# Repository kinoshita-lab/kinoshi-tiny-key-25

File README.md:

# Kinoshi-Tiny Key 25
[日本語の説明はこちら](./README.ja.md)

----

## What is this?

- A small MIDI keyboard, 106 mm x 50 mm.
- Has USB MIDI (In/Out) and legacy MIDI (Out, 3.5 mm Type A).
- It has:
  - Octave switches +/-
  - Modulation switch
  - Pitch Bend switches
  - Sustain switch

- The source code and schematics are open. You can change them as you need.

## What's in the box
- DIN-TRS adapter cable (Type A)
- Rubber feet (use them if you need them)

## How to use
- Power it with a USB Type-C cable. Connect it to a mobile battery, a PC/Mac, etc.
- USB MIDI works with the standard OS driver. No extra driver is needed.

## Settings editor
- A web-browser-based editor lets you change the MIDI channels, velocity, button behavior and more.
- https://kinoshi-tiny-key-25.editor.kinoshita-lab.com/
- Requires firmware v1.1.0 or later.

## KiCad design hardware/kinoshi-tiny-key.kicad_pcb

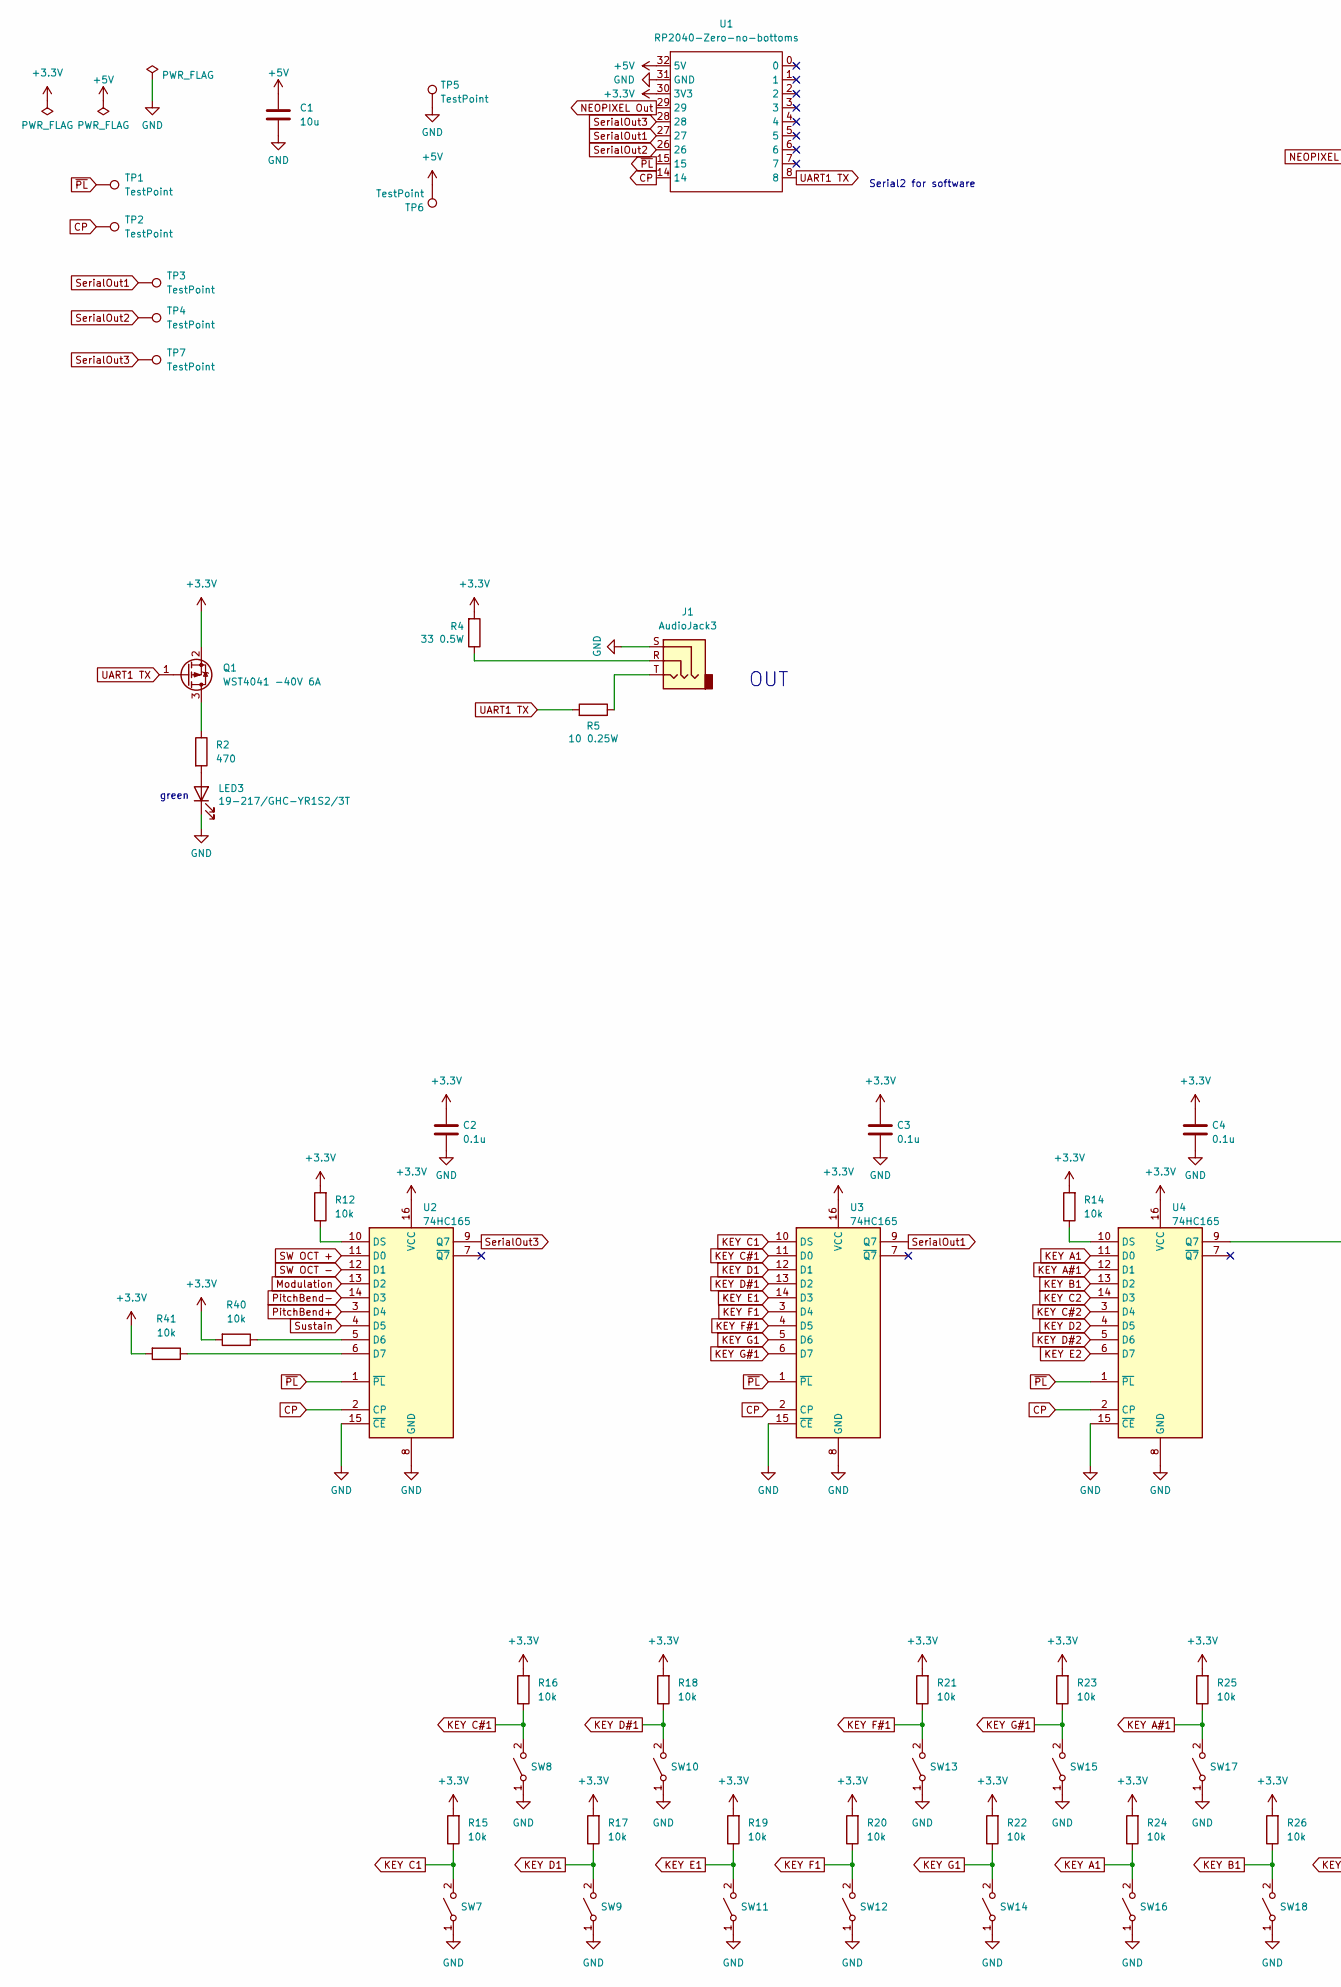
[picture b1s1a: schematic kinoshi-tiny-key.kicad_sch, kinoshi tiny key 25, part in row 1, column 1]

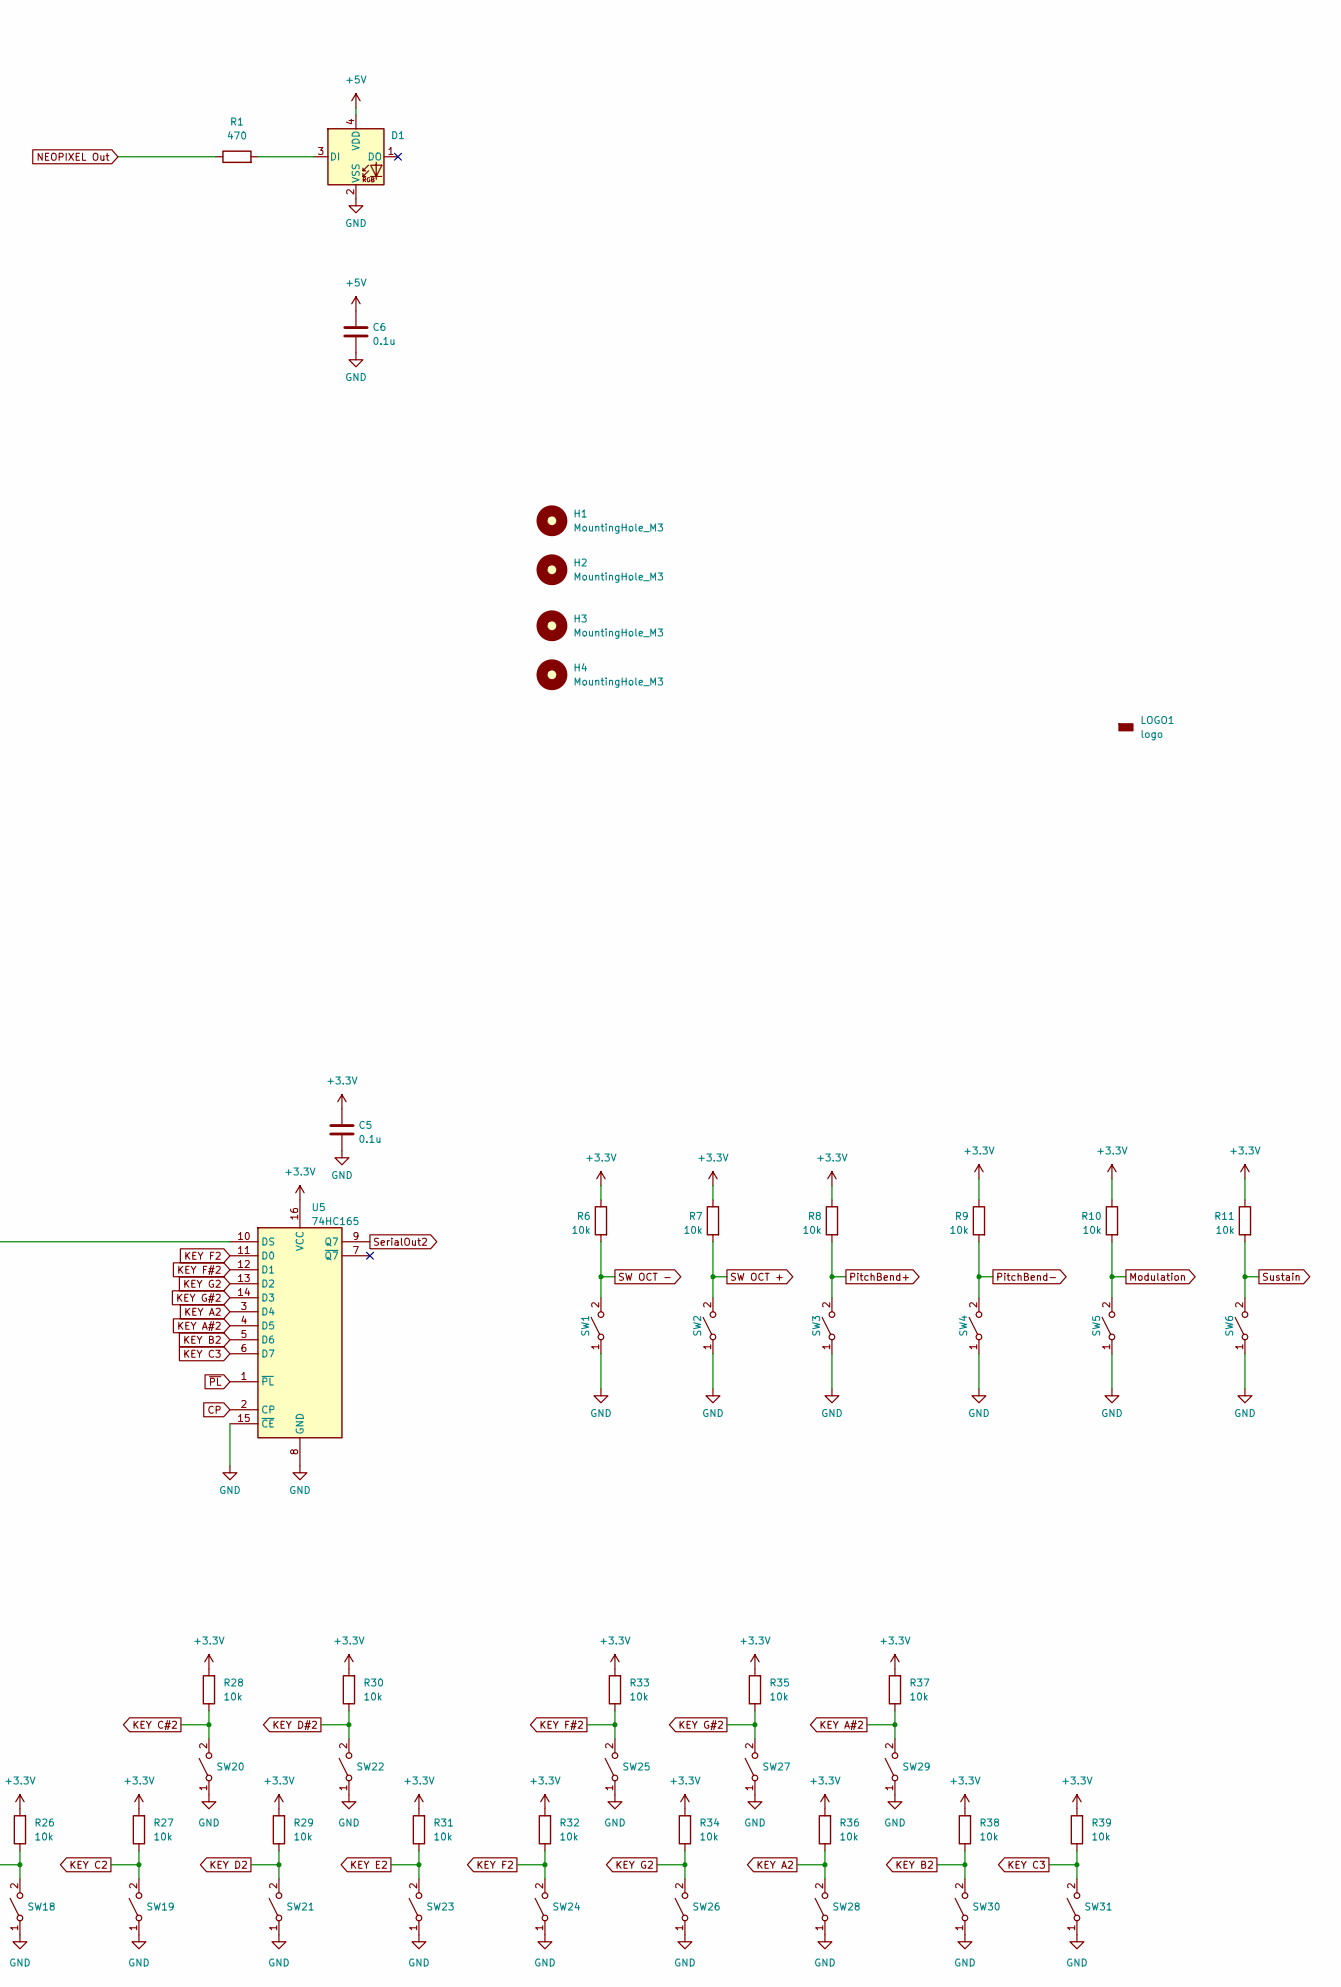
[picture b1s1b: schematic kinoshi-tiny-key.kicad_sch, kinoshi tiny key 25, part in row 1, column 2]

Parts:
C1: 10u; C_1206_3216Metric_Pad1.33x1.80mm_HandSolder; LCSC C13585
C2, C3, C4, C5, C6: 0.1u; C_0402_1005Metric_Pad0.74x0.62mm_HandSolder; LCSC C1525
D1: LED_NeoPixel_CHONGTIAN_CT-1615UGRBC/H-P6-5_C52191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; LED_NeoPixel_CHONGTIAN CT-1615UGRBCH-P6-5_C52191312; LCSC C52191312
H1, H2, H3, H4: MountingHole_M3; MountingHole_2.2mm_M2
J1: AudioJack3; 3.5mm_Stereo_TRS_PJ-3210-4A_and_ST-005-G; LCSC C136686
LED3: 19-217/GHC-YR1S2/3T; LED_0603_1608Metric_Pad1.05x0.95mm_HandSolder; LCSC C72043
LOGO1: logo; kinoshita-logo_simplified_300dpi
Q1: WST4041 -40V 6A; SOT-23; LCSC C148357
R1: 470; R_0603_1608Metric; LCSC C23179
R2: 470; R_0402_1005Metric; LCSC C25117
R4: 33 0.5W; R_1210_3225Metric_Pad1.30x2.65mm_HandSolder; LCSC C407192
R5: 10 0.25W; R_1206_3216Metric_Pad1.30x1.75mm_HandSolder; LCSC C17903
R6, R7, R8, R9, R10, R11: 10k; R_0402_1005Metric_Pad0.72x0.64mm_HandSolder; LCSC C25744
R12, R14, R15, R16, R17, R18, R19, R20, R21, R22, R23, R24, R25, R26, R27, R28, R29, R30, R31, R32, R33, R34, R35, R36, R37, R38, R39, R40, R41: 10k; R_0402_1005Metric; LCSC C25744
SW1, SW2, SW3, SW4, SW5, SW6: SW_SPST; Switch_Tactile_TS1187A26017_C22459525; LCSC C22459525
SW7, SW8, SW9, SW10, SW11, SW12, SW13, SW14, SW15, SW16, SW17, SW18, SW19, SW20, SW21, SW22, SW23, SW24, SW25, SW26, SW27, SW28, SW29, SW30, SW31: SW_SPST; Switch_Tactile_TSB008A2518A_C2888455; LCSC C2888456
TP1, TP2, TP3, TP4, TP5, TP6, TP7: TestPoint; TestPoint_THTPad_1.0x1.0mm_Drill0.5mm
U1: RP2040-Zero-no-bottoms; RP2040-Zero-THT-no-bottoms
U2, U3, U4, U5: 74HC165; TSSOP-16_4.4x5mm_P0.65mm; LCSC C80696

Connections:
+3.3V: C2.1, C3.1, C4.1, C5.1, Q1.2 (S), R4.2, R6.1, R7.1, R8.1, R9.1, R10.1, R11.1, R12.2, R14.2, R15.2, R16.2, R17.2, R18.2, R19.2, R20.2, R21.2, R22.2, R23.2, R24.2, R25.2, R26.2, R27.2, R28.2, R29.2, R30.2, R31.2, R32.2, R33.2, R34.2, R35.2, R36.2, R37.2, R38.2, R39.2, R40.2, R41.2, U1.30 (3V3), U2.16 (VCC), U3.16 (VCC), U4.16 (VCC), U5.16 (VCC)
+5V: C1.1, C6.1, D1.4 (VDD), TP6.1 (1_1), U1.32 (5V)
CP: TP2.1 (1_1), U1.14, U2.2 (CP), U3.2 (CP), U4.2 (CP), U5.2 (CP)
GND: C1.2, C2.2, C3.2, C4.2, C5.2, C6.2, D1.2 (VSS), J1.S, LED3.1 (K), SW1.1 (A), SW2.1 (A), SW3.1 (A), SW4.1 (A), SW5.1 (A), SW6.1 (A), SW7.1 (A), SW8.1 (A), SW9.1 (A), SW10.1 (A), SW11.1 (A), SW12.1 (A), SW13.1 (A), SW14.1 (A), SW15.1 (A), SW16.1 (A), SW17.1 (A), SW18.1 (A), SW19.1 (A), SW20.1 (A), SW21.1 (A), SW22.1 (A), SW23.1 (A), SW24.1 (A), SW25.1 (A), SW26.1 (A), SW27.1 (A), SW28.1 (A), SW29.1 (A), SW30.1 (A), SW31.1 (A), TP5.1 (1_1), U1.31 (GND), U2.8 (GND), U2.15 (~CE), U3.8 (GND), U3.15 (~CE), U4.8 (GND), U4.15 (~CE), U5.8 (GND), U5.15 (~CE)
KEY A1: R24.1, SW16.2 (B), U4.11 (D0)
KEY A2: R36.1, SW28.2 (B), U5.3 (D4)
KEY A#1: R25.1, SW17.2 (B), U4.12 (D1)
KEY A#2: R37.1, SW29.2 (B), U5.4 (D5)
KEY B1: R26.1, SW18.2 (B), U4.13 (D2)
KEY B2: R38.1, SW30.2 (B), U5.5 (D6)
KEY C1: R15.1, SW7.2 (B), U3.10 (DS)
KEY C2: R27.1, SW19.2 (B), U4.14 (D3)
KEY C3: R39.1, SW31.2 (B), U5.6 (D7)
KEY C#1: R16.1, SW8.2 (B), U3.11 (D0)
KEY C#2: R28.1, SW20.2 (B), U4.3 (D4)
KEY D1: R17.1, SW9.2 (B), U3.12 (D1)
KEY D2: R29.1, SW21.2 (B), U4.4 (D5)
KEY D#1: R18.1, SW10.2 (B), U3.13 (D2)
KEY D#2: R30.1, SW22.2 (B), U4.5 (D6)
KEY E1: R19.1, SW11.2 (B), U3.14 (D3)
KEY E2: R31.1, SW23.2 (B), U4.6 (D7)
KEY F1: R20.1, SW12.2 (B), U3.3 (D4)
KEY F2: R32.1, SW24.2 (B), U5.11 (D0)
KEY F#1: R21.1, SW13.2 (B), U3.4 (D5)
KEY F#2: R33.1, SW25.2 (B), U5.12 (D1)
KEY G1: R22.1, SW14.2 (B), U3.5 (D6)
KEY G2: R34.1, SW26.2 (B), U5.13 (D2)
KEY G#1: R23.1, SW15.2 (B), U3.6 (D7)
KEY G#2: R35.1, SW27.2 (B), U5.14 (D3)
Modulation: R10.2, SW5.2 (B), U2.13 (D2)
NEOPIXEL Out: R1.1, U1.29
unnamed: D1.3 (DI), R1.2
unnamed: J1.R, R4.1
unnamed: J1.T, R5.1
unnamed: LED3.2 (A), R2.2
unnamed: Q1.3 (D), R2.1
unnamed: R40.1, U2.5 (D6)
unnamed: R41.1, U2.6 (D7)
unnamed: R12.1, U2.10 (DS)
unnamed: R14.1, U4.10 (DS)
unnamed: U4.9 (Q7), U5.10 (DS)
PitchBend+: R8.2, SW3.2 (B), U2.3 (D4)
PitchBend-: R9.2, SW4.2 (B), U2.14 (D3)
SW OCT +: R7.2, SW2.2 (B), U2.11 (D0)
SW OCT -: R6.2, SW1.2 (B), U2.12 (D1)
SerialOut1: TP3.1 (1_1), U1.27, U3.9 (Q7)
SerialOut2: TP4.1 (1_1), U1.26, U5.9 (Q7)
SerialOut3: TP7.1 (1_1), U1.28, U2.9 (Q7)
Sustain: R11.2, SW6.2 (B), U2.4 (D5)
UART1 TX: Q1.1 (G), R5.2, U1.8
~PL: TP1.1 (1_1), U1.15, U2.1 (~PL), U3.1 (~PL), U4.1 (~PL), U5.1 (~PL)

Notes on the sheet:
OUT
Serial2 for software
green

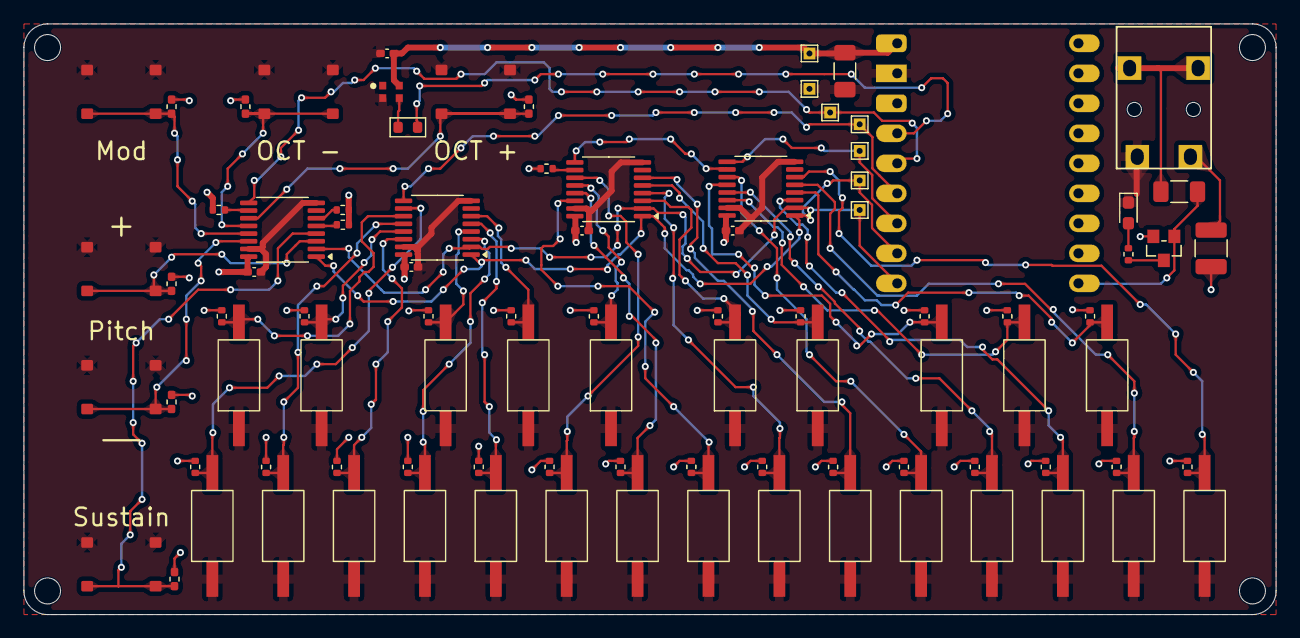
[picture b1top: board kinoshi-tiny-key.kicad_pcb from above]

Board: 2 copper layers, 106.0 x 50.0 mm, 97 parts (1 on the bottom side), 51 nets.

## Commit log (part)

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2025-09-21 implementing software
2025-09-21 give up submodule
2025-10-02 soft: implement basic specifications
2025-10-02 hardware: add files
2025-10-02 hard: add pdfs
2025-10-02 Add MIT License to the project
2025-10-03 soft: rename product
2025-10-03 soft: add todo
2025-10-03 doc: add documents
